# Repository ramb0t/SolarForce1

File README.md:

# SolarForce1
Team Work for SF1

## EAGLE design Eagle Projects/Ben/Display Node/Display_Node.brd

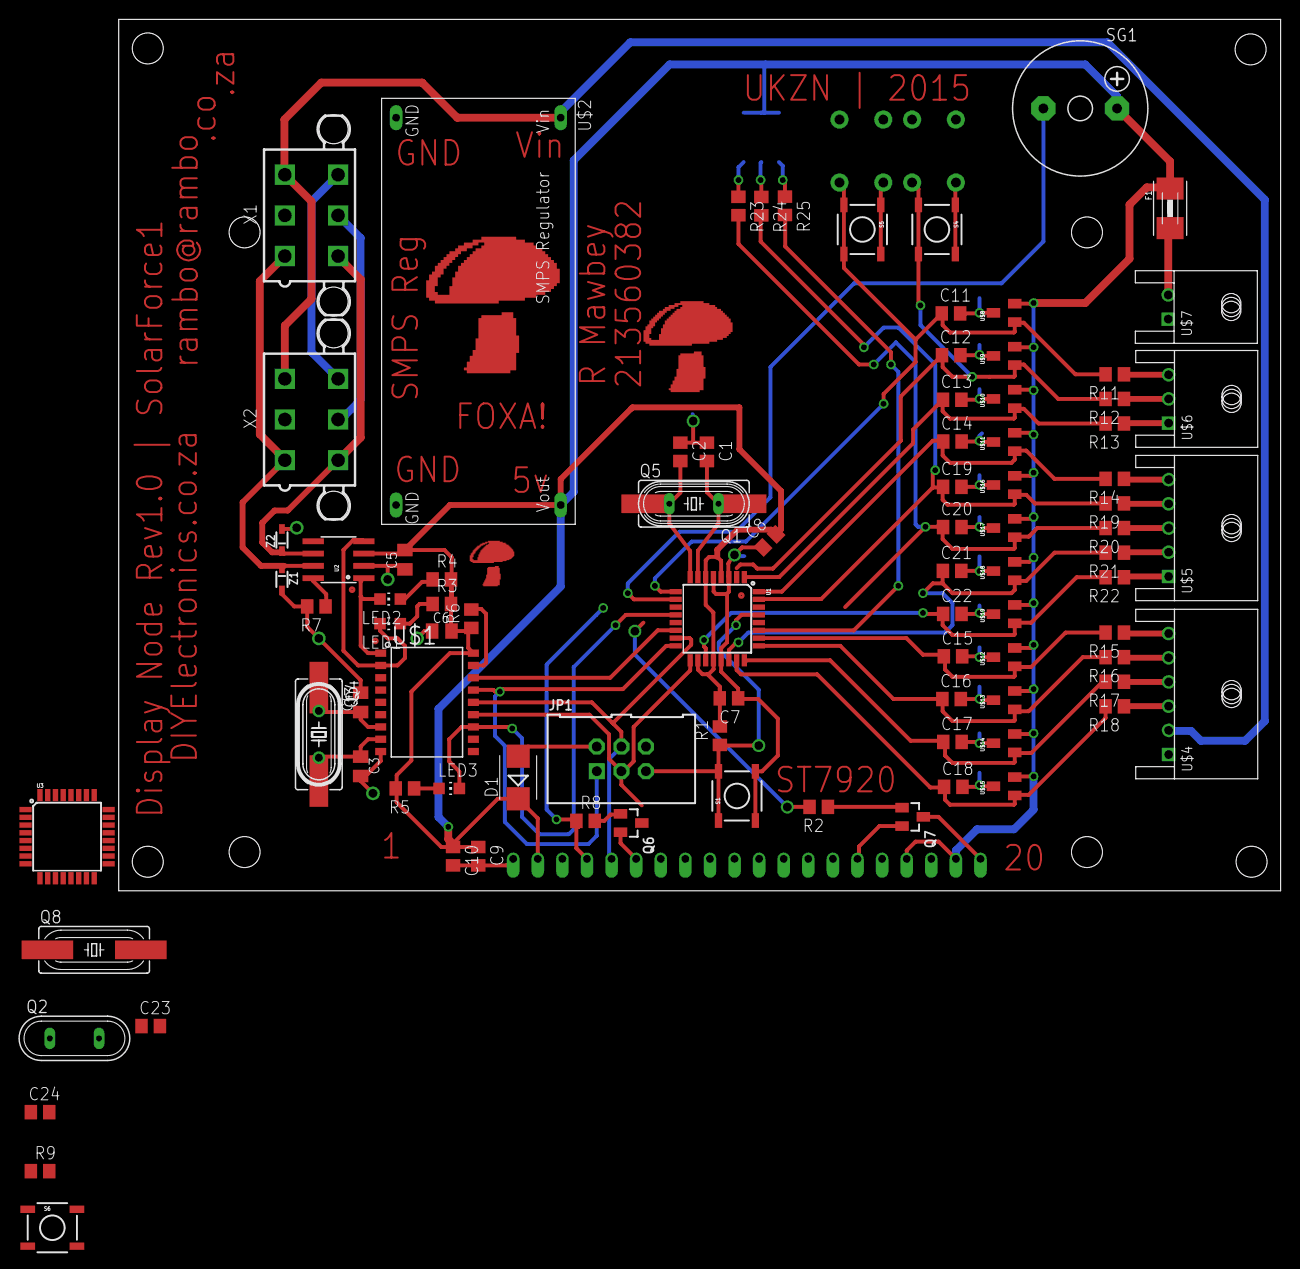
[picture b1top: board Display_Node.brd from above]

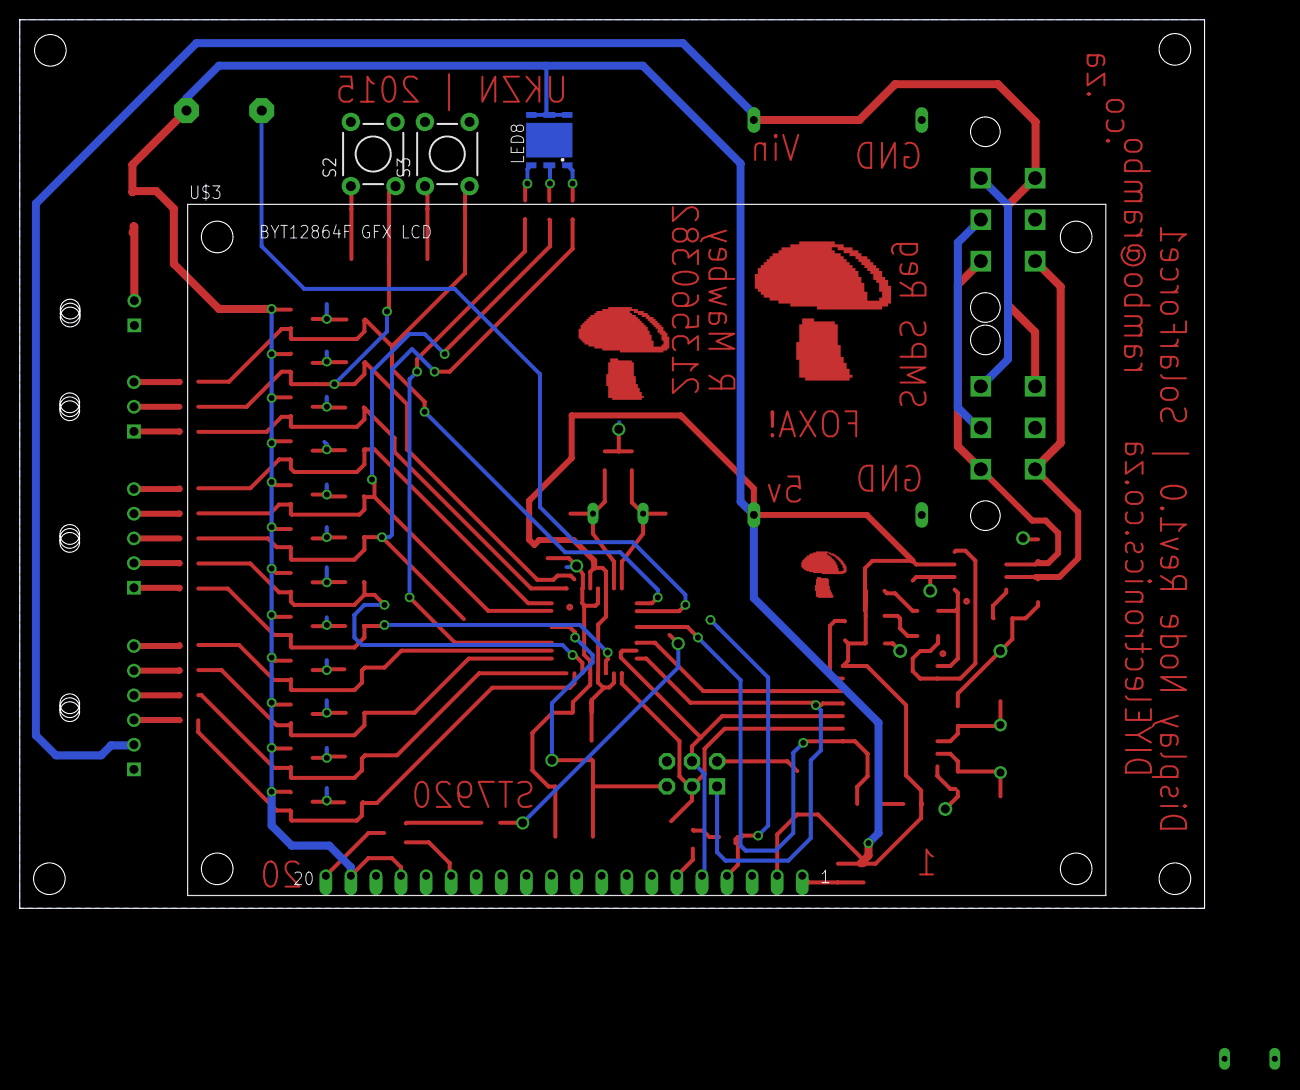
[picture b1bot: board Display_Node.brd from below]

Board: 2 copper layers, 120.0 x 90.0 mm, 96 parts (4 on the bottom side), 69 nets.

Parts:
C1, C2, C23, C24: 22pF; C0805
C3, C4: 22pF; C0805K
C5, C6: 100nF; C0805K
C7, C8, C9: 100nF; C0805
C10: 10uF; C0805
C11, C12, C13, C14, C15, C16, C17, C18, C19, C20, C21, C22: 10nF; C0805
D1: SMB
F1: 1812
JP1: AVRISP6; HDR-75869-131
LED1: RX; CHIP-LED0805
LED2: TX; CHIP-LED0805
LED3: INT; CHIP-LED0805
LED8: F50360
Q1, Q2: 16MHz; QS
Q3: 16MHz; HC49/S
Q4, Q5, Q8: 16MHz; HC49UP
Q6, Q7: 2N7002; SOT23
R1, R9: 50k; R0805
R2, R8: 100E; R0805
R3, R4, R5, R23, R24, R25: 1k; R0805
R6, R7: 100k; R0805
R11, R12, R13, R14, R15, R16, R17, R18, R19, R20, R21, R22: 470E; R0805
S1, S6: RESET; TACTILE_SWITCH_SMD
S2, S3: SWITCH-MOMENTARY-2PTH; TACTILE-PTH
S4: BTN3; TACTILE_SWITCH_SMD
S5: BTN4; TACTILE_SWITCH_SMD
SG1: F/CM12P
U1, U3: ATMEGA328P_TQFP; TQFP32-08
U2: MCP2551; SO08
U$1: MCP2515SO; SO-18W
U$2: SMPSBOARD
U$3: BYT12864FLCD; BYT12864F
U$4: HEADER-6WAY; 1744426-6
U$5: HEADER-5WAY; 1744426-5
U$6: HEADER-3WAY; 1744426-3
U$7: HEADER-2WAY; 1744426-2
U$8, U$9, U$10, U$11, U$12, U$13, U$14, U$15, U$16, U$17, U$18, U$19: DRTR5V0U1SO; SOT23
X1, X2: 5566-6
Z1, Z2: TVS-UD-SOD323; SOD323

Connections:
+5V: C5.2, C6.2, C7.2, C8.2, C9.1, C10.1, D1.C, F1.1, LED8.BA, LED8.GA, LED8.RA, R1.2, R3.2, R4.2, R5.2, R6.1, R9.2, SG1.+, U1.4, U1.6, U1.18, U1.20, U2.3, U$1.18, U$2.VOUT, U$3.P$2, U$3.P$4, U$3.P$19, U$8.2, U$9.2, U$10.2, U$11.2, U$12.2, U$13.2, U$14.2, U$15.2, U$16.2, U$17.2, U$18.2, U$19.2
+12V: U$2.VIN, U$4.P$2, X1.3, X2.3
A0: C22.1, R22.2, U1.19, U$19.1
A1: C21.1, R21.2, U1.22, U$18.1
BTN1: C14.1, R14.2, U1.32, U$11.1
BTN2: C13.1, R13.2, U1.1, U$10.1
BTN3: C12.1, R12.2, S2.3, S4.3, S4.4, U$9.1
BTN4: C11.1, R11.2, S3.3, S5.3, S5.4, U1.9, U$8.1
CANCS: U1.14, U$1.16
CANH: U2.7, X1.1, X2.1, Z1.C
CANINT: LED3.C, U1.12, U$1.12
CANL: U2.6, X1.4, X2.4, Z2.C
CANRST: R6.2, U$1.17
CANSTBY: R7.1, U2.8
CRUISE1: C18.1, R18.2, U1.23, U$15.1
CRUISE2: C17.1, R17.2, U1.24, U$14.1
CRUISE3: C16.1, R16.2, U1.25, U$13.1
CRUISE4: C15.1, R15.2, U1.26, U$12.1
GND: C1.1, C2.1, C3.2, C4.2, C5.1, C6.1, C7.1, C8.1, C9.2, C10.2, C11.2, C12.2, C13.2, C14.2, C15.2, C16.2, C17.2, C18.2, C19.2, C20.2, C21.2, C22.2, C23.1, C24.1, JP1.6, Q7.2, R7.2, S1.3, S1.4, S2.1, S3.1, S4.1, S4.2, S5.1, S5.2, S6.3, S6.4, U1.3, U1.5, U1.21, U2.2, U$1.9, U$2.GND, U$2.GND@, U$3.P$6, U$3.P$20, U$4.P$1, U$7.P$1, U$8.3, U$9.3, U$10.3, U$11.3, U$12.3, U$13.3, U$14.3, U$15.3, U$16.3, U$17.3, U$18.3, U$19.3, X1.2, X2.2, Z1.A, Z2.A
LCD_CS: R8.1, U3.11, U$3.P$17
LCD_PWM: R2.2, U3.13
LED1: C20.1, R20.2, R23.2, U$17.1
LED2: C19.1, R19.2, R24.2, U$16.1
LED3: R25.2, U1.27
MISO: JP1.1, U1.16, U$1.15
MISOU: U1.30, U3.30
MOSI: JP1.4, U1.15, U$1.14
MOSI2: U3.15, U$3.P$16
MOSIU: U1.31, U3.31
unnamed: C1.2, Q1.1, Q5.2, U1.7
unnamed: C2.2, Q1.2, Q5.1, U1.8
unnamed: C3.1, Q3.2, Q4.2, U$1.8
unnamed: Q7.3, U$3.P$1
unnamed: Q7.1, R2.1
unnamed: C4.1, Q3.1, Q4.1, U$1.7
unnamed: LED1.A, R3.1
unnamed: LED2.A, R4.1
unnamed: LED3.A, R5.1
unnamed: D1.A, JP1.2
unnamed: Q6.2, U$3.P$15
unnamed: Q6.1, R8.2
unnamed: X1.5, X2.5
unnamed: X1.6, X2.6
unnamed: F1.2, U$7.P$2
unnamed: R11.1, U$6.P$3
unnamed: R12.1, U$6.P$2
unnamed: R13.1, U$6.P$1
unnamed: R14.1, U$5.P$5
unnamed: R18.1, U$4.P$3
unnamed: R17.1, U$4.P$4
unnamed: R16.1, U$4.P$5
unnamed: R15.1, U$4.P$6
unnamed: R19.1, U$5.P$4
unnamed: R20.1, U$5.P$3
unnamed: R21.1, U$5.P$2
unnamed: R22.1, U$5.P$1
unnamed: SG1.-, U1.10
unnamed: LED8.RC, R23.1
unnamed: LED8.GC, R24.1
unnamed: LED8.BC, R25.1
unnamed: C23.2, Q2.1, Q8.2, U3.7
unnamed: C24.2, Q2.2, Q8.1, U3.8
RST: JP1.5, R1.1, S1.1, S1.2, U1.29
RST1: R9.1, S6.1, S6.2
RXCAN: LED1.C, U2.4, U$1.2
SCK: JP1.3, U1.17, U$1.13
SCK2: Q6.3, U3.17
SCKU: U1.2, U3.2
TXCAN: LED2.C, U2.1, U$1.1

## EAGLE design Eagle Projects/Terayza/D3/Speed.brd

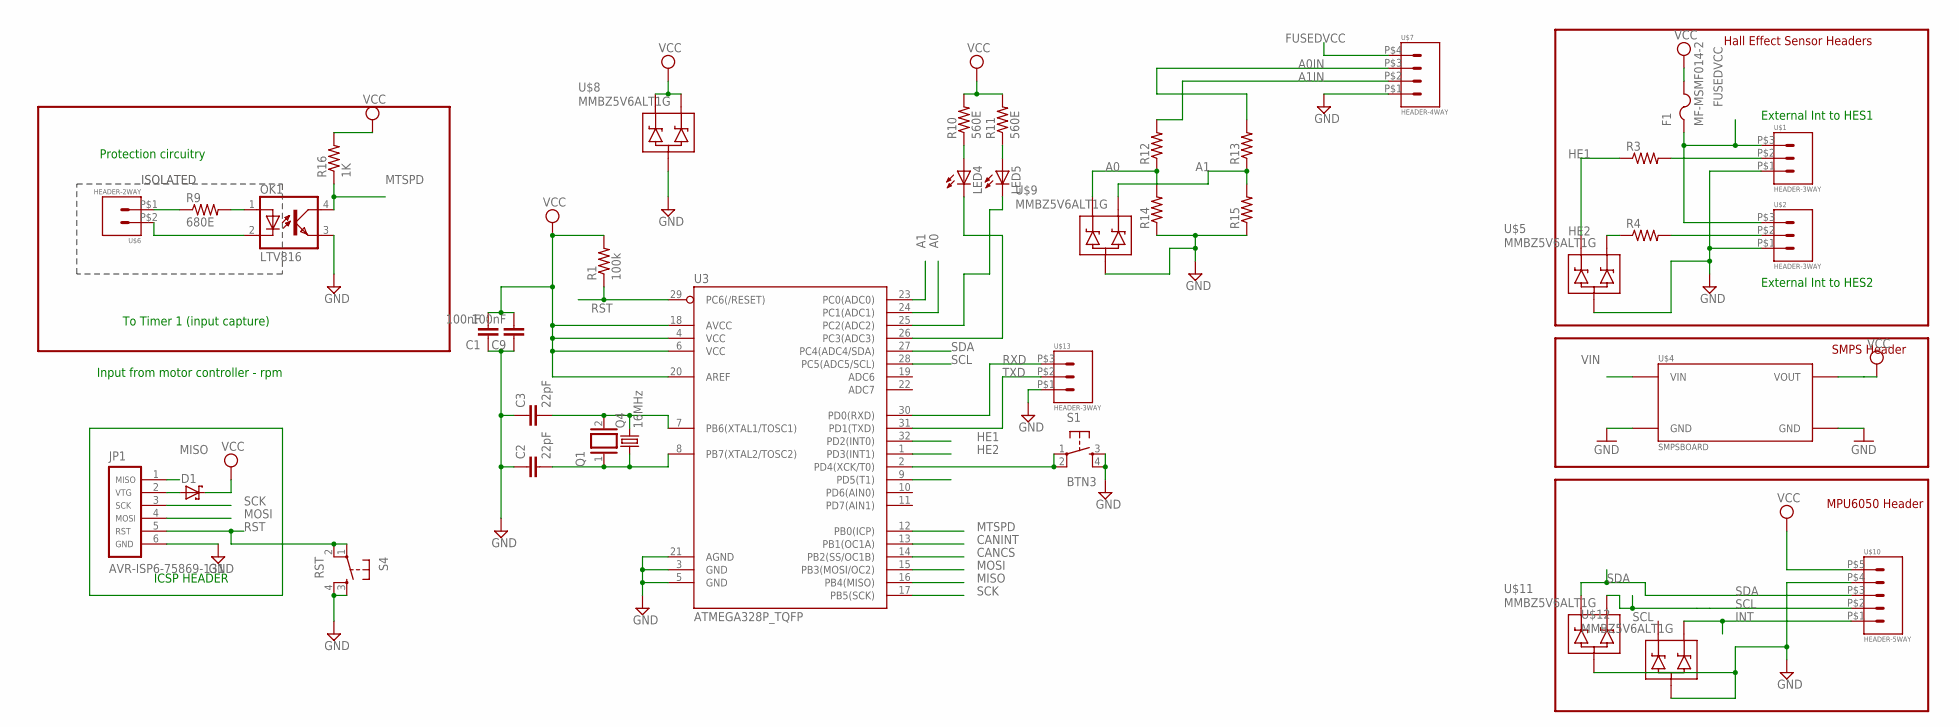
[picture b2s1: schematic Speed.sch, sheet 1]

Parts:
C1, C9: 100nF; C0805
C2, C3: 22pF; C0805
D1: SCHOTTKY-DIODESMD; SMB
F1: MF-MSMF014-2; 1812
JP1: AVR-ISP6-75869-131; HDR-75869-131
LED4, LED5: LEDCHIP-LED0805; CHIP-LED0805
OK1: LTV816; DIL04
Q1: XTAL/S; QS
Q4: 16MHz; HC49UP
R1: 100k; M0805
R3, R4, R12, R13, R14, R15: R-US_M0805; M0805
R9: 680E; M0805
R10, R11: 560E; M0805
R16: 1K; M0805
S1: BTN3; TACTILE_SWITCH_SMD
S4: RST; TACTILE_SWITCH_SMD
U3: ATMEGA328P_TQFP; TQFP32-08
U$1, U$2, U$13: HEADER-3WAY; 1744426-3
U$4: SMPSBOARD
U$5, U$8, U$9, U$11, U$12: MMBZ5V6ALT1G; SOT23
U$6: HEADER-2WAY; 1744426-2
U$7: HEADER-4WAY; 1744426-4
U$10: HEADER-5WAY; 1744426-5

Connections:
A0: R12.1, R14.2, U3.24 (PC1(ADC1)), U$9.2 (A2)
A0IN: R13.2, U$7.P$3
A1: R13.1, R15.2, U3.23 (PC0(ADC0)), U$9.1 (A1)
A1IN: R12.2, U$7.P$2
CANCS: U3.14 (PB2(SS/OC1B)); also elsewhere on the board
CANINT: U3.13 (PB1(OC1A)); also elsewhere on the board
FUSEDVCC: F1.1, U$1.P$3, U$2.P$3, U$7.P$4
GND: C1.1, C2.1, C3.1, C9.1, JP1.6, OK1.3 (EMIT), R14.1, R15.1, S1.3, S1.4, S4.3, S4.4, U3.3 (GND), U3.5 (GND), U3.21 (AGND), U$1.P$1, U$2.P$1, U$4.GND, U$4.GND@ (GND), U$5.3 (C), U$7.P$1, U$8.3 (C), U$9.3 (C), U$10.P$4, U$11.3 (C), U$12.3 (C), U$13.P$1; also elsewhere on the board
HE1: R3.1, U3.32 (PD2(INT0)), U$5.2 (A2)
HE2: R4.1, U3.1 (PD3(INT1)), U$5.1 (A1)
INT: U3.9 (PD5(T1)), U$10.P$1, U$12.1 (A1)
MISO: JP1.1, U3.16 (PB4(MISO)); also elsewhere on the board
MOSI: JP1.4, U3.15 (PB3(MOSI/OC2)); also elsewhere on the board
MTSPD: OK1.4 (COL), R16.1, U3.12 (PB0(ICP))
unnamed: D1.A, JP1.2
unnamed: R9.1, U$6.P$1
unnamed: OK1.1 (A), R9.2
unnamed: C3.2, Q1.2, Q4.2, U3.7 (PB6(XTAL1/TOSC1))
unnamed: C2.2, Q1.1, Q4.1, U3.8 (PB7(XTAL2/TOSC2))
unnamed: LED4.A, R10.1
unnamed: LED5.A, R11.1
unnamed: LED5.C, U3.25 (PC2(ADC2))
unnamed: LED4.C, U3.26 (PC3(ADC3))
unnamed: S1.1, S1.2, U3.2 (PD4(XCK/T0))
unnamed: OK1.2 (C), U$6.P$2
PD2: R3.2, U$1.P$2
PD3: R4.2, U$2.P$2
RST: JP1.5, R1.1, S4.1, S4.2, U3.29 (PC6(/RESET))
RXD: U3.30 (PD0(RXD)), U$13.P$3
SCK: JP1.3, U3.17 (PB5(SCK)); also elsewhere on the board
SCL: U3.28 (PC5(ADC5/SCL)), U$10.P$2, U$11.1 (A1)
SDA: U3.27 (PC4(ADC4/SDA)), U$10.P$3, U$11.2 (A2)
TXD: U3.31 (PD1(TXD)), U$13.P$2
VCC: C1.2, C9.2, D1.C, F1.2, R1.2, R10.2, R11.2, R16.2, U3.4 (VCC), U3.6 (VCC), U3.18 (AVCC), U3.20 (AREF), U$4.VOUT, U$8.1 (A1), U$8.2 (A2), U$10.P$5; also elsewhere on the board
VIN: U$4.VIN; also elsewhere on the board

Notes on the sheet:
Input from motor controller - rpm
To Timer 1 (input capture)
Protection circuitry
External Int to HES1
External Int to HES2
Hall Effect Sensor Headers
SMPS Header
ICSP HEADER
ISOLATED
MPU6050 Header

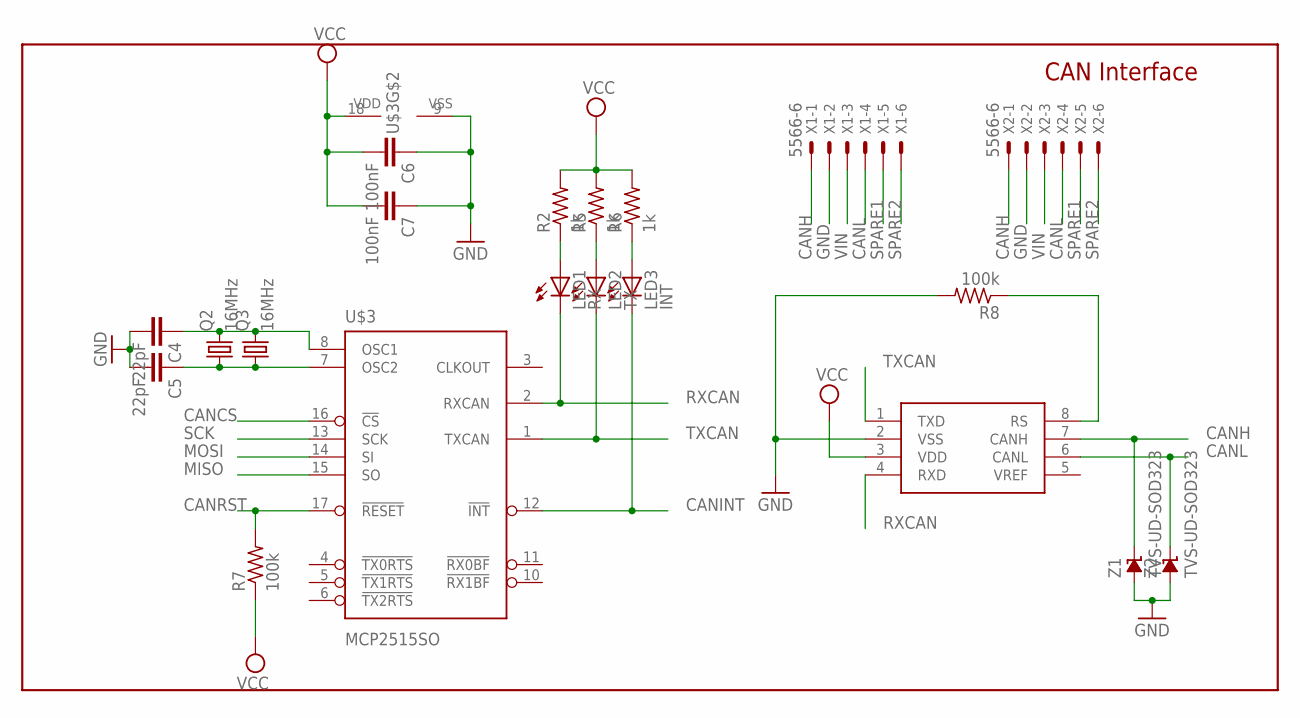
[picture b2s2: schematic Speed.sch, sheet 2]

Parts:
C4, C5: 22pF; C0805K
C6, C7: 100nF; C0805K
LED1: RX; CHIP-LED0805
LED2: TX; CHIP-LED0805
LED3: INT; CHIP-LED0805
Q2: 16MHz; HC49/S
Q3: 16MHz; HC49UP
R2, R5, R6: 1k; R0805
R7, R8: 100k; R0805
U2: MCP2551; SO08
U$3: MCP2515SO; SO-18W
X1, X2: 5566-6
Z1, Z2: TVS-UD-SOD323; SOD323

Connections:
CANCS: U$3.16 (!CS); also elsewhere on the board
CANH: U2.7 (CANH), X1.1, X2.1, Z1.C
CANINT: LED3.C, U$3.12 (!INT); also elsewhere on the board
CANL: U2.6 (CANL), X1.4, X2.4, Z2.C
CANRST: R7.2, U$3.17 (!RESET)
CANSTBY: R8.1, U2.8 (RS)
GND: C4.2, C5.2, C6.1, C7.1, R8.2, U2.2 (VSS), U$3.9 (VSS), X1.2, X2.2, Z1.A, Z2.A; also elsewhere on the board
MISO: U$3.15 (SO); also elsewhere on the board
MOSI: U$3.14 (SI); also elsewhere on the board
unnamed: LED1.A, R2.1
unnamed: LED2.A, R5.1
unnamed: LED3.A, R6.1
unnamed: C4.1, Q2.2, Q3.2, U$3.8 (OSC1)
unnamed: C5.1, Q2.1, Q3.1, U$3.7 (OSC2)
RXCAN: LED1.C, U2.4 (RXD), U$3.2 (RXCAN)
SCK: U$3.13 (SCK); also elsewhere on the board
SPARE1: X1.5, X2.5
SPARE2: X1.6, X2.6
TXCAN: LED2.C, U2.1 (TXD), U$3.1 (TXCAN)
VCC: C6.2, C7.2, R2.2, R5.2, R6.2, R7.1, U2.3 (VDD), U$3.18 (VDD); also elsewhere on the board
VIN: X1.3, X2.3; also elsewhere on the board

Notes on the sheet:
CAN Interface

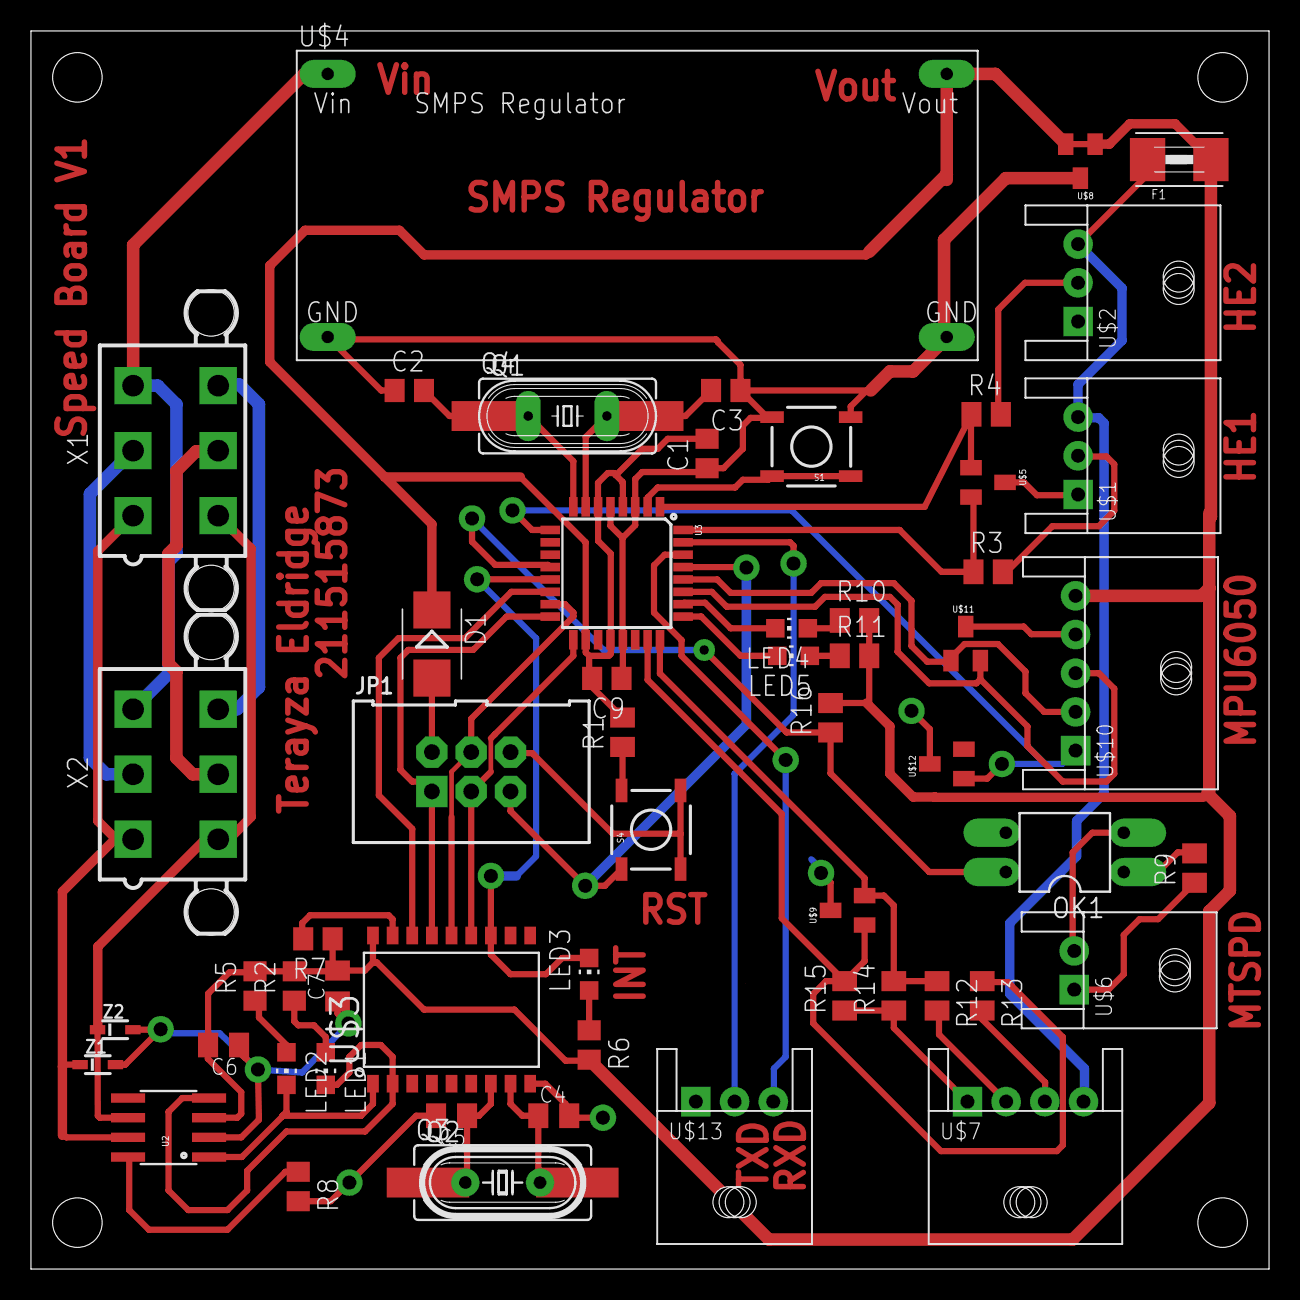
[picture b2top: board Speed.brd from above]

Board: 2 copper layers, 80.0 x 80.0 mm, 58 parts (0 on the bottom side), 48 nets.

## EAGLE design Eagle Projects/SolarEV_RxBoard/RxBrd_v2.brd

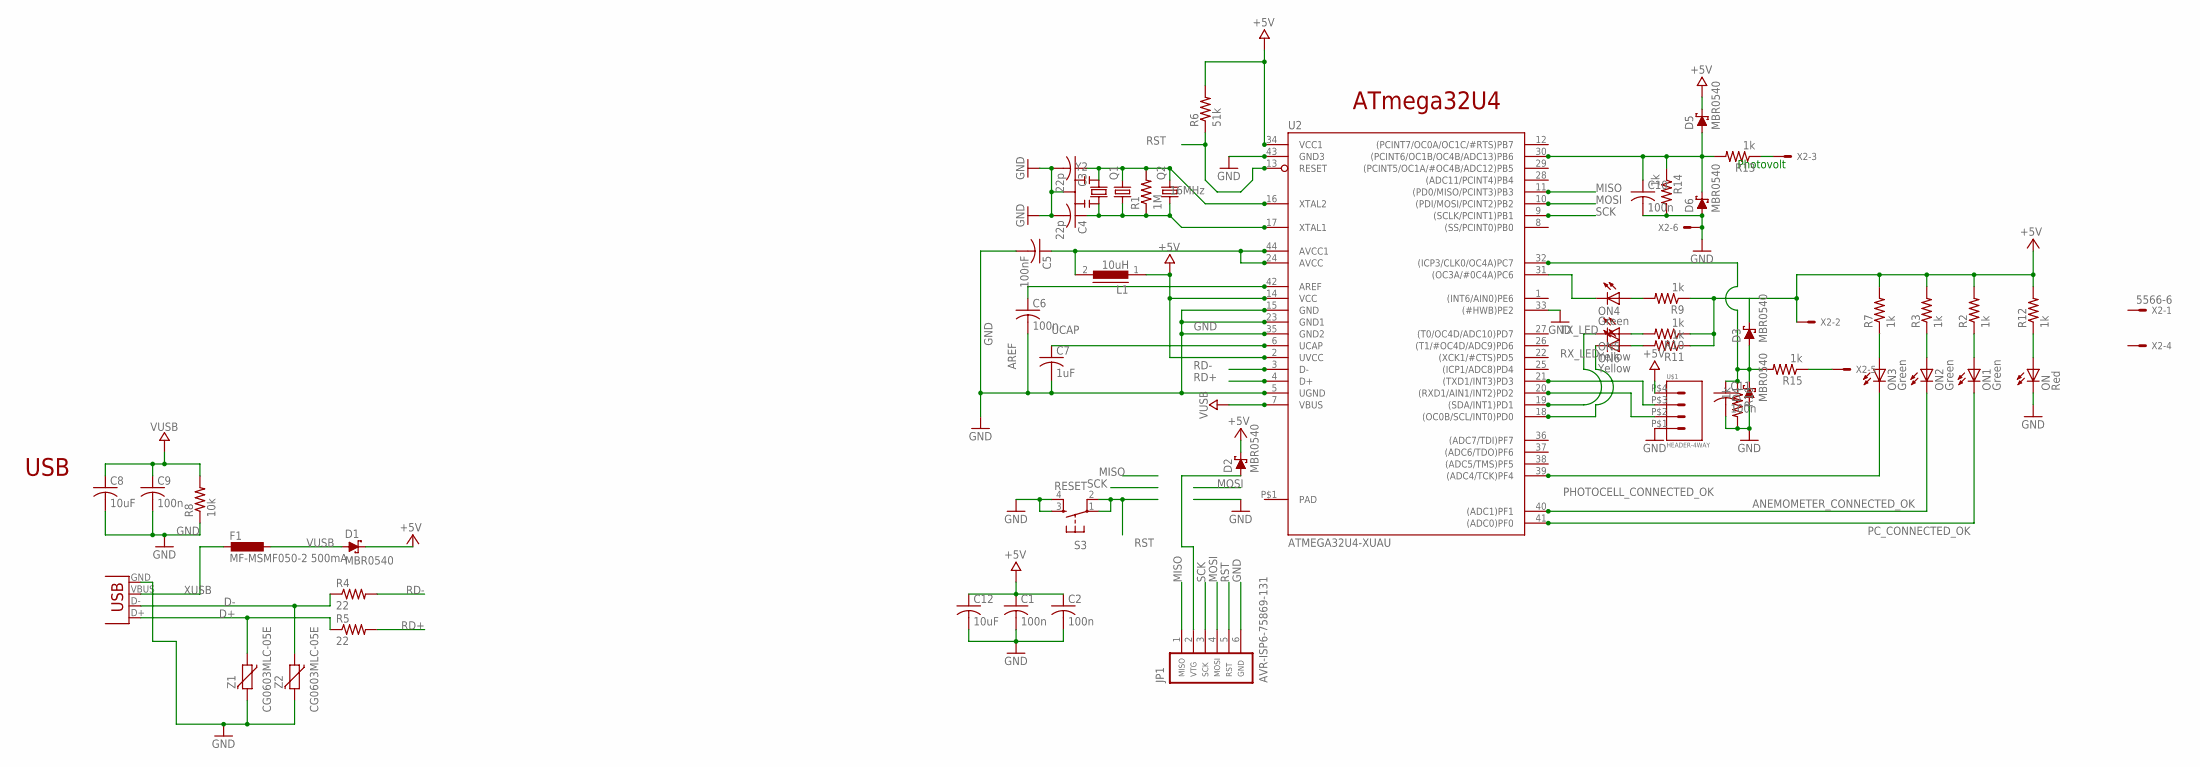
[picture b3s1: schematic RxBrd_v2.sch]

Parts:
C1, C2, C6, C9, C10, C11: 100n; C0805
C3, C4: 22p; C0805
C5: 100nF; C0805
C7: 1uF; C0805
C8, C12: 10uF; C0805
D1, D2, D3, D4, D5, D6: MBR0540; SOD123@2
F1: MF-MSMF050-2 500mA; L1812
JP1: AVR-ISP6-75869-131; HDR-75869-131
L1: 10uH; MMICC7
ON: Red; CHIPLED_0805
ON1, ON2, ON3, ON4: Green; CHIPLED_0805
ON5, ON6: Yellow; CHIPLED_0805
Q1: CRYSTALHC49UP; HC49UP
Q2: CRYSTALHC49S; HC49/S
R1: 1M; R0805
R2, R3, R7, R9, R10, R11, R12, R13, R14, R15, R16: 1k; R0805
R4, R5: 22; R0805
R6: 51k; R0805
R8: 10k; R0805
S3: RESET; TACTILE_SWITCH_SMD
U2: ATMEGA32U4-XUAU; TQFP44-PAD
U$1: HEADER-4WAY; 1744426-4
X1: USBPTH; USB-B-PTH
X2: 5566-6
Y2: 16MHz; RESONATOR
Z1, Z2: CG0603MLC-05E; CT/CN0603

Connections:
+5V: C1.1, C2.1, C12.1, D1.C, D2.C, D3.C, D5.C, L1.1, R2.2, R3.2, R6.2, R7.2, R9.1, R10.1, R11.1, R12.2, U2.2 (UVCC), U2.14 (VCC), U2.34 (VCC1), U$1.P$4, X2.2
ANEMOMETER_CONNECTED_OK: ON2.C, U2.40 ((ADC1)PF1)
AREF: C6.1, U2.42 (AREF)
AVCC: C5.1, L1.2, U2.24 (AVCC), U2.44 (AVCC1)
D+: R5.1, X1.D+, Z1.1
D-: R4.1, X1.D-, Z2.1
GND: C1.2, C2.2, C3.2, C4.2, C5.2, C6.2, C7.2, C8.2, C9.2, C10.2, C11.2, C12.2, D4.A, D6.A, JP1.6, ON.C, R8.1, R14.2, R16.2, S3.3, S3.4, U2.5 (UGND), U2.15 (GND), U2.23 (GND1), U2.33 ((#HWB)PE2), U2.35 (GND2), U2.43 (GND3), U$1.P$1, X1.GND, X2.6, Y2.2, Z1.2, Z2.2
MISO: JP1.1, U2.11 ((PD0/MISO/PCINT3)PB3)
MOSI: JP1.4, U2.10 ((PDI/MOSI/PCINT2)PB2)
unnamed: C11.1, D3.A, D4.C, R15.2, R16.1, U2.32 ((ICP3/CLK0/OC4A)PC7)
unnamed: ON3.A, R7.1
unnamed: ON.A, R12.1
unnamed: R13.1, X2.3
unnamed: C10.1, D5.A, D6.C, R13.2, R14.1, U2.30 ((PCINT6/OC1B/OC4B/ADC13)PB6)
unnamed: ON4.A, R9.2
unnamed: U2.20 ((RXD1/AIN1/INT2)PD2), U$1.P$2
unnamed: U2.21 ((TXD1/INT3)PD3), U$1.P$3
unnamed: ON2.A, R3.1
unnamed: D2.A, JP1.2
unnamed: ON1.A, R2.1
unnamed: ON5.A, R10.2
unnamed: ON4.C, U2.31 ((OC3A/#0C4A)PC6)
unnamed: ON6.A, R11.2
unnamed: R15.1, X2.5
PAD: U2.P$1 (PAD)
PC_CONNECTED_OK: ON1.C, U2.41 ((ADC0)PF0)
PHOTOCELL_CONNECTED_OK: ON3.C, U2.39 ((ADC4/TCK)PF4)
RD+: R5.2, U2.4 (D+)
RD-: R4.2, U2.3 (D-)
RST: JP1.5, R6.1, S3.1, S3.2, U2.13 (RESET)
RX_LED: ON6.C, U2.18 ((OC0B/SCL/INT0)PD0)
SCK: JP1.3, U2.9 ((SCLK/PCINT1)PB1)
TX_LED: ON5.C, U2.19 ((SDA/INT1)PD1)
UCAP: C7.1, U2.6 (UCAP)
VUSB: C8.1, C9.1, D1.A, F1.1, R8.2, U2.7 (VBUS)
XTAL1: C4.1, Q1.1, Q2.1, R1.1, U2.17 (XTAL1), Y2.3
XTAL2: C3.1, Q1.2, Q2.2, R1.2, U2.16 (XTAL2), Y2.1
XUSB: F1.2, X1.VBUS

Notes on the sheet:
USB
ATmega32U4
Photovolt

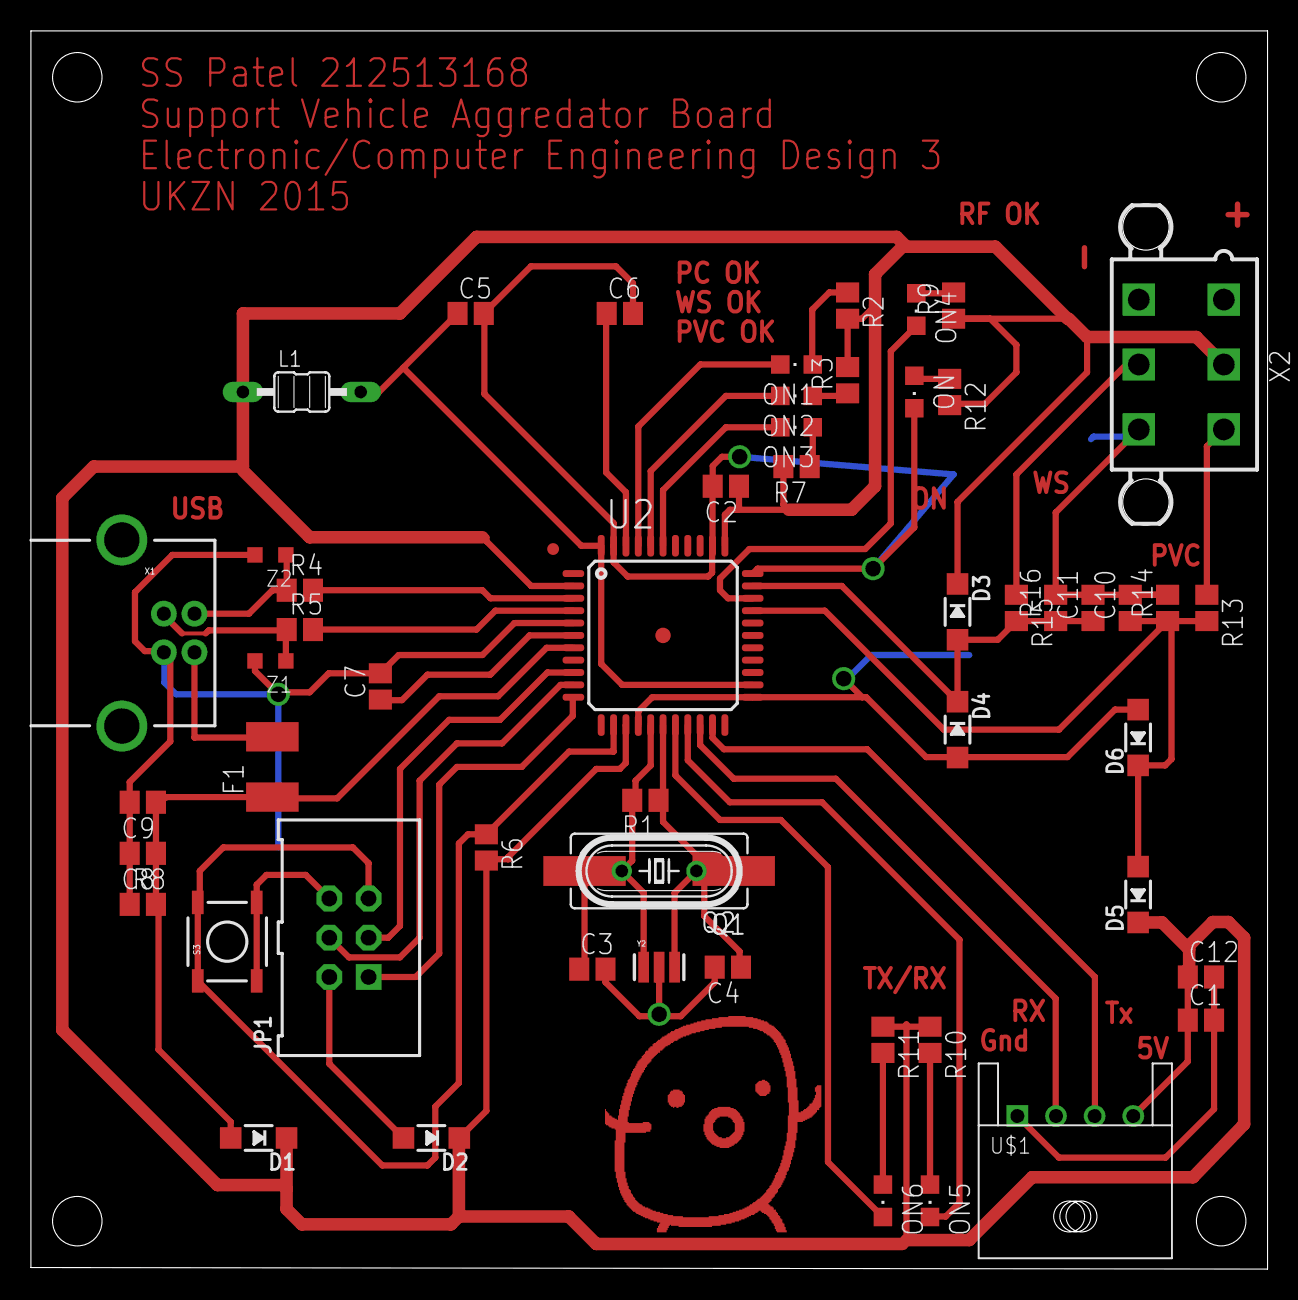
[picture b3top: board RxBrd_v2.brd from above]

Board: 2 copper layers, 80.0 x 80.1 mm, 54 parts (0 on the bottom side), 37 nets.

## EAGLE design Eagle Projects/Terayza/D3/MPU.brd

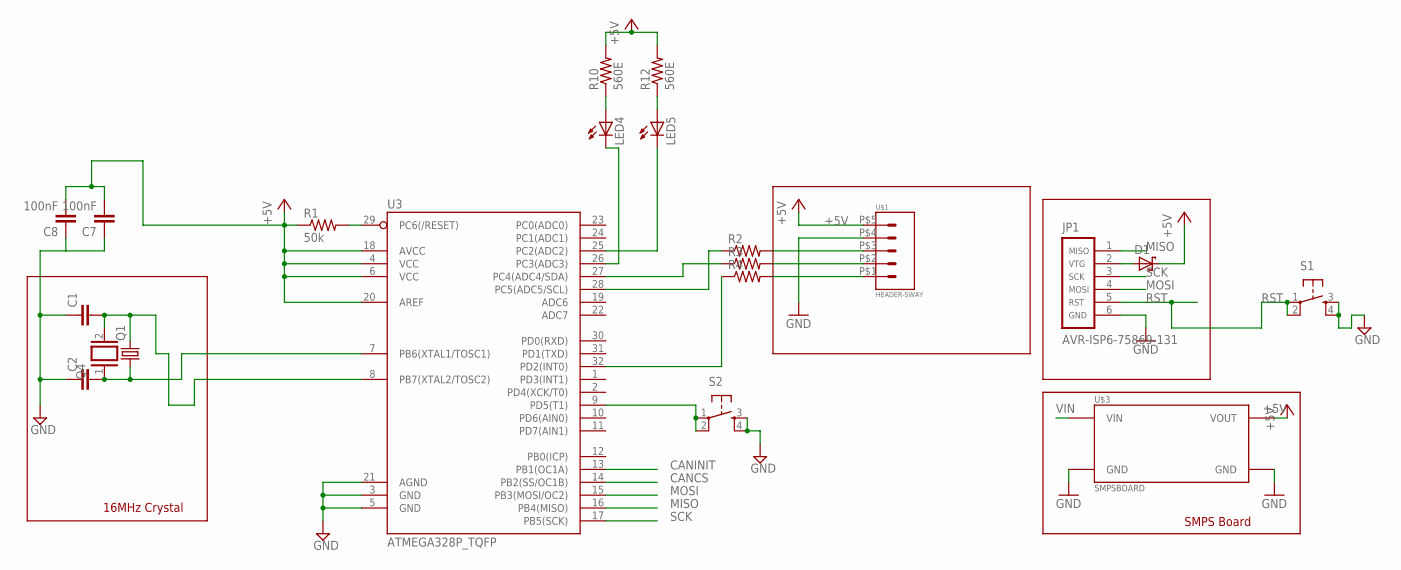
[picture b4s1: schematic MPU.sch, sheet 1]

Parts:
C1, C2: C-EUC0805; C0805
C7, C8: 100nF; C0805
D1: SCHOTTKY-DIODESMD; SMB
JP1: AVR-ISP6-75869-131; HDR-75869-131
LED4, LED5: LEDCHIP-LED0805; CHIP-LED0805
Q1: CRYSTALHC49UP; HC49UP
Q4: XTAL/S; QS
R1: 50k; M0805
R2, R3, R4: R-US_M0805; M0805
R10, R12: 560E; M0805
S1, S2: TAC_SWITCHSMD; TACTILE_SWITCH_SMD
U3: ATMEGA328P_TQFP; TQFP32-08
U$1: HEADER-5WAY; 1744426-5
U$3: SMPSBOARD

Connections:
+5V: C7.2, C8.2, D1.C, R1.1, R10.2, R12.2, U3.4 (VCC), U3.6 (VCC), U3.18 (AVCC), U3.20 (AREF), U$1.P$5, U$3.VOUT; also elsewhere on the board
CANCS: U3.14 (PB2(SS/OC1B)); also elsewhere on the board
CANINIT: U3.13 (PB1(OC1A))
GND: C1.1, C2.1, C7.1, C8.1, JP1.6, S1.3, S1.4, S2.3, S2.4, U3.3 (GND), U3.5 (GND), U3.21 (AGND), U$1.P$4, U$3.GND, U$3.GND@ (GND); also elsewhere on the board
INT: R4.2, U$1.P$1
MISO: JP1.1, U3.16 (PB4(MISO)); also elsewhere on the board
MOSI: JP1.4, U3.15 (PB3(MOSI/OC2)); also elsewhere on the board
unnamed: R2.1, U3.28 (PC5(ADC5/SCL))
unnamed: R3.1, U3.27 (PC4(ADC4/SDA))
unnamed: R4.1, U3.32 (PD2(INT0))
unnamed: LED5.C, U3.25 (PC2(ADC2))
unnamed: C2.2, Q1.1, Q4.1, U3.7 (PB6(XTAL1/TOSC1))
unnamed: S2.1, S2.2, U3.9 (PD5(T1))
unnamed: R1.2, U3.29 (PC6(/RESET))
unnamed: LED4.A, R10.1
unnamed: LED5.A, R12.1
unnamed: LED4.C, U3.26 (PC3(ADC3))
unnamed: D1.A, JP1.2
unnamed: C1.2, Q1.2, Q4.2, U3.8 (PB7(XTAL2/TOSC2))
RST: JP1.5, S1.1, S1.2
SCK: JP1.3, U3.17 (PB5(SCK)); also elsewhere on the board
SCL: R2.2, U$1.P$3
SDA: R3.2, U$1.P$2
VIN: U$3.VIN; also elsewhere on the board

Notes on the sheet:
16MHz Crystal
SMPS Board

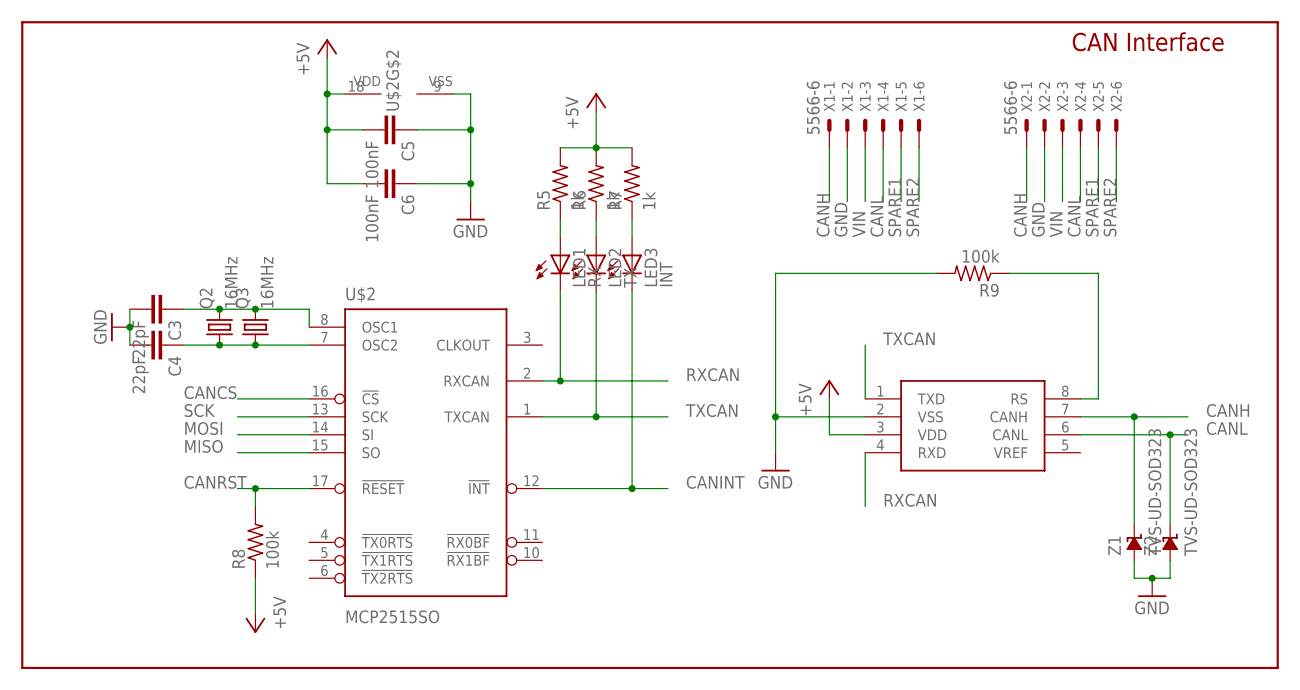
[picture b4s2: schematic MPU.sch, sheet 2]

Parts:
C3, C4: 22pF; C0805K
C5, C6: 100nF; C0805K
LED1: RX; CHIP-LED0805
LED2: TX; CHIP-LED0805
LED3: INT; CHIP-LED0805
Q2: 16MHz; HC49/S
Q3: 16MHz; HC49UP
R5, R6, R7: 1k; R0805
R8, R9: 100k; R0805
U2: MCP2551; SO08
U$2: MCP2515SO; SO-18W
X1, X2: 5566-6
Z1, Z2: TVS-UD-SOD323; SOD323

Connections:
+5V: C5.2, C6.2, R5.2, R6.2, R7.2, R8.1, U2.3 (VDD), U$2.18 (VDD); also elsewhere on the board
CANCS: U$2.16 (!CS); also elsewhere on the board
CANH: U2.7 (CANH), X1.1, X2.1, Z1.C
CANINT: LED3.C, U$2.12 (!INT)
CANL: U2.6 (CANL), X1.4, X2.4, Z2.C
CANRST: R8.2, U$2.17 (!RESET)
CANSTBY: R9.1, U2.8 (RS)
GND: C3.2, C4.2, C5.1, C6.1, R9.2, U2.2 (VSS), U$2.9 (VSS), X1.2, X2.2, Z1.A, Z2.A; also elsewhere on the board
MISO: U$2.15 (SO); also elsewhere on the board
MOSI: U$2.14 (SI); also elsewhere on the board
unnamed: LED1.A, R5.1
unnamed: LED2.A, R6.1
unnamed: LED3.A, R7.1
unnamed: C3.1, Q2.2, Q3.2, U$2.8 (OSC1)
unnamed: C4.1, Q2.1, Q3.1, U$2.7 (OSC2)
RXCAN: LED1.C, U2.4 (RXD), U$2.2 (RXCAN)
SCK: U$2.13 (SCK); also elsewhere on the board
SPARE1: X1.5, X2.5
SPARE2: X1.6, X2.6
TXCAN: LED2.C, U2.1 (TXD), U$2.1 (TXCAN)
VIN: X1.3, X2.3; also elsewhere on the board

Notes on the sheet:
CAN Interface

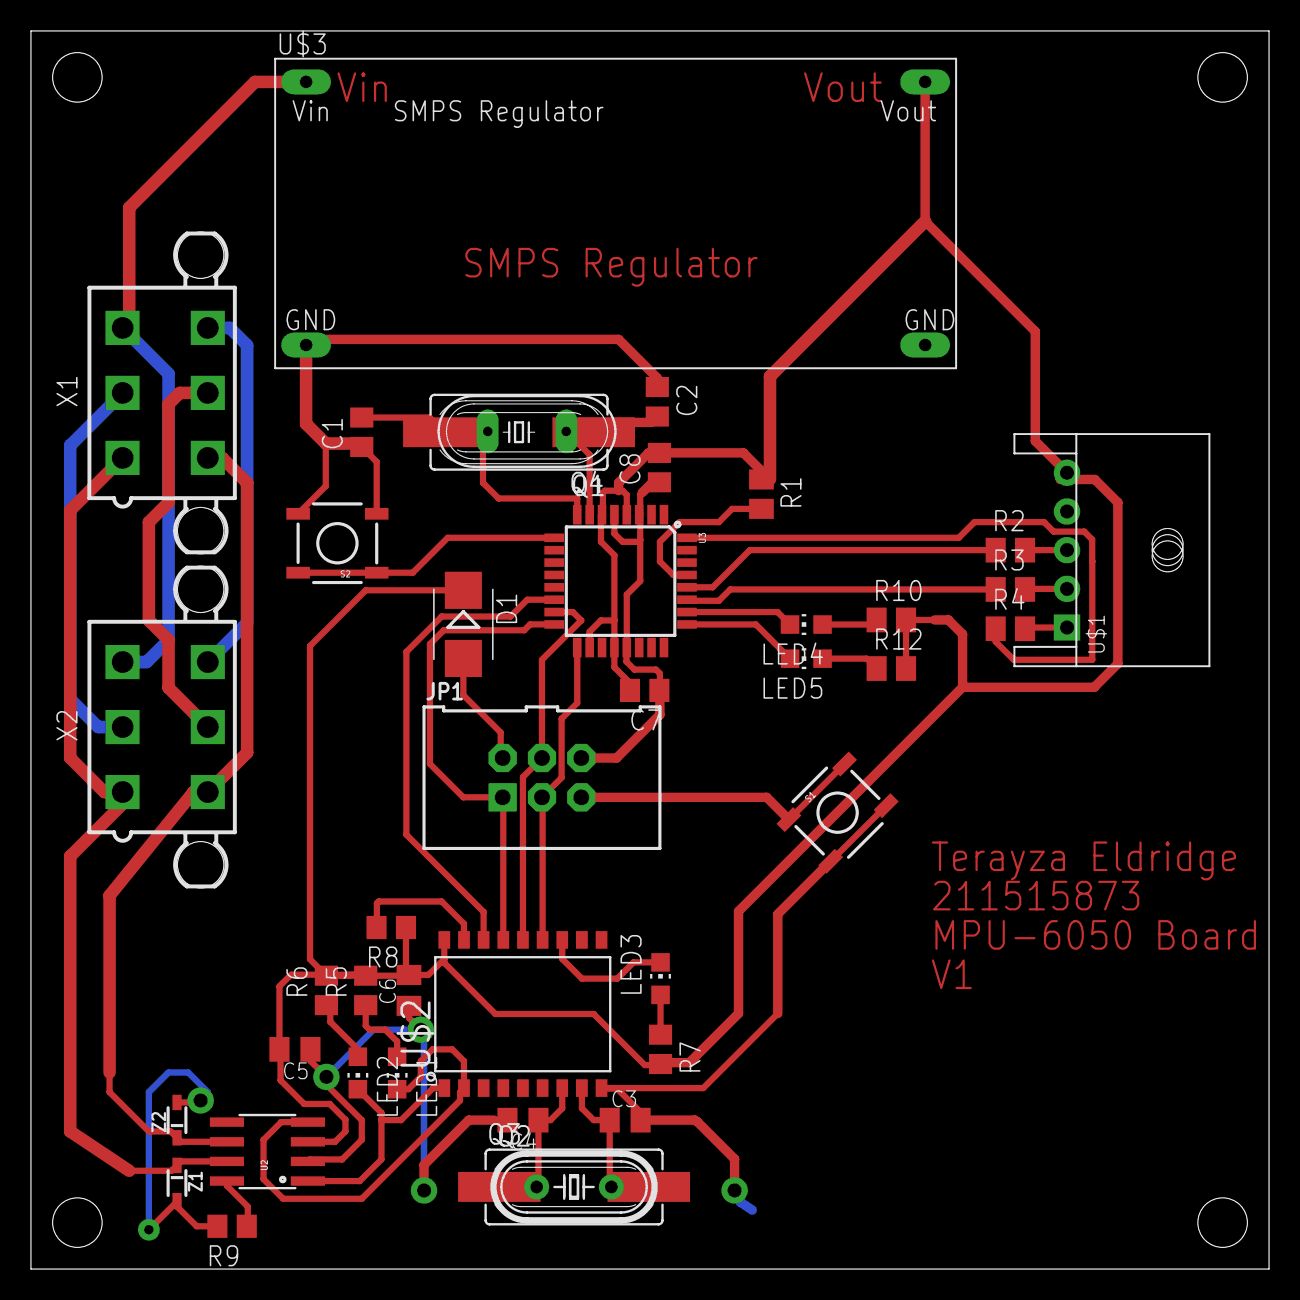
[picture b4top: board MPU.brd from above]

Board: 2 copper layers, 80.0 x 80.0 mm, 41 parts (0 on the bottom side), 37 nets.

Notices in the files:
CAN Embedded/SD_Node/sdmm.c:
Copyright (C) 2013, ChaN, all right reserved.
parts and their libraries:
SparkFun: Licensing: CC v3.0 Share-Alike You are welcome to use this library for commercial purposes.
supressor: Copyright (C) 2009, Bob Starr
SparkFun-DigitalIC: Licensing: Creative Commons ShareAlike 4.0 International - https://creativecommons.org/licenses/by-sa/4.0
